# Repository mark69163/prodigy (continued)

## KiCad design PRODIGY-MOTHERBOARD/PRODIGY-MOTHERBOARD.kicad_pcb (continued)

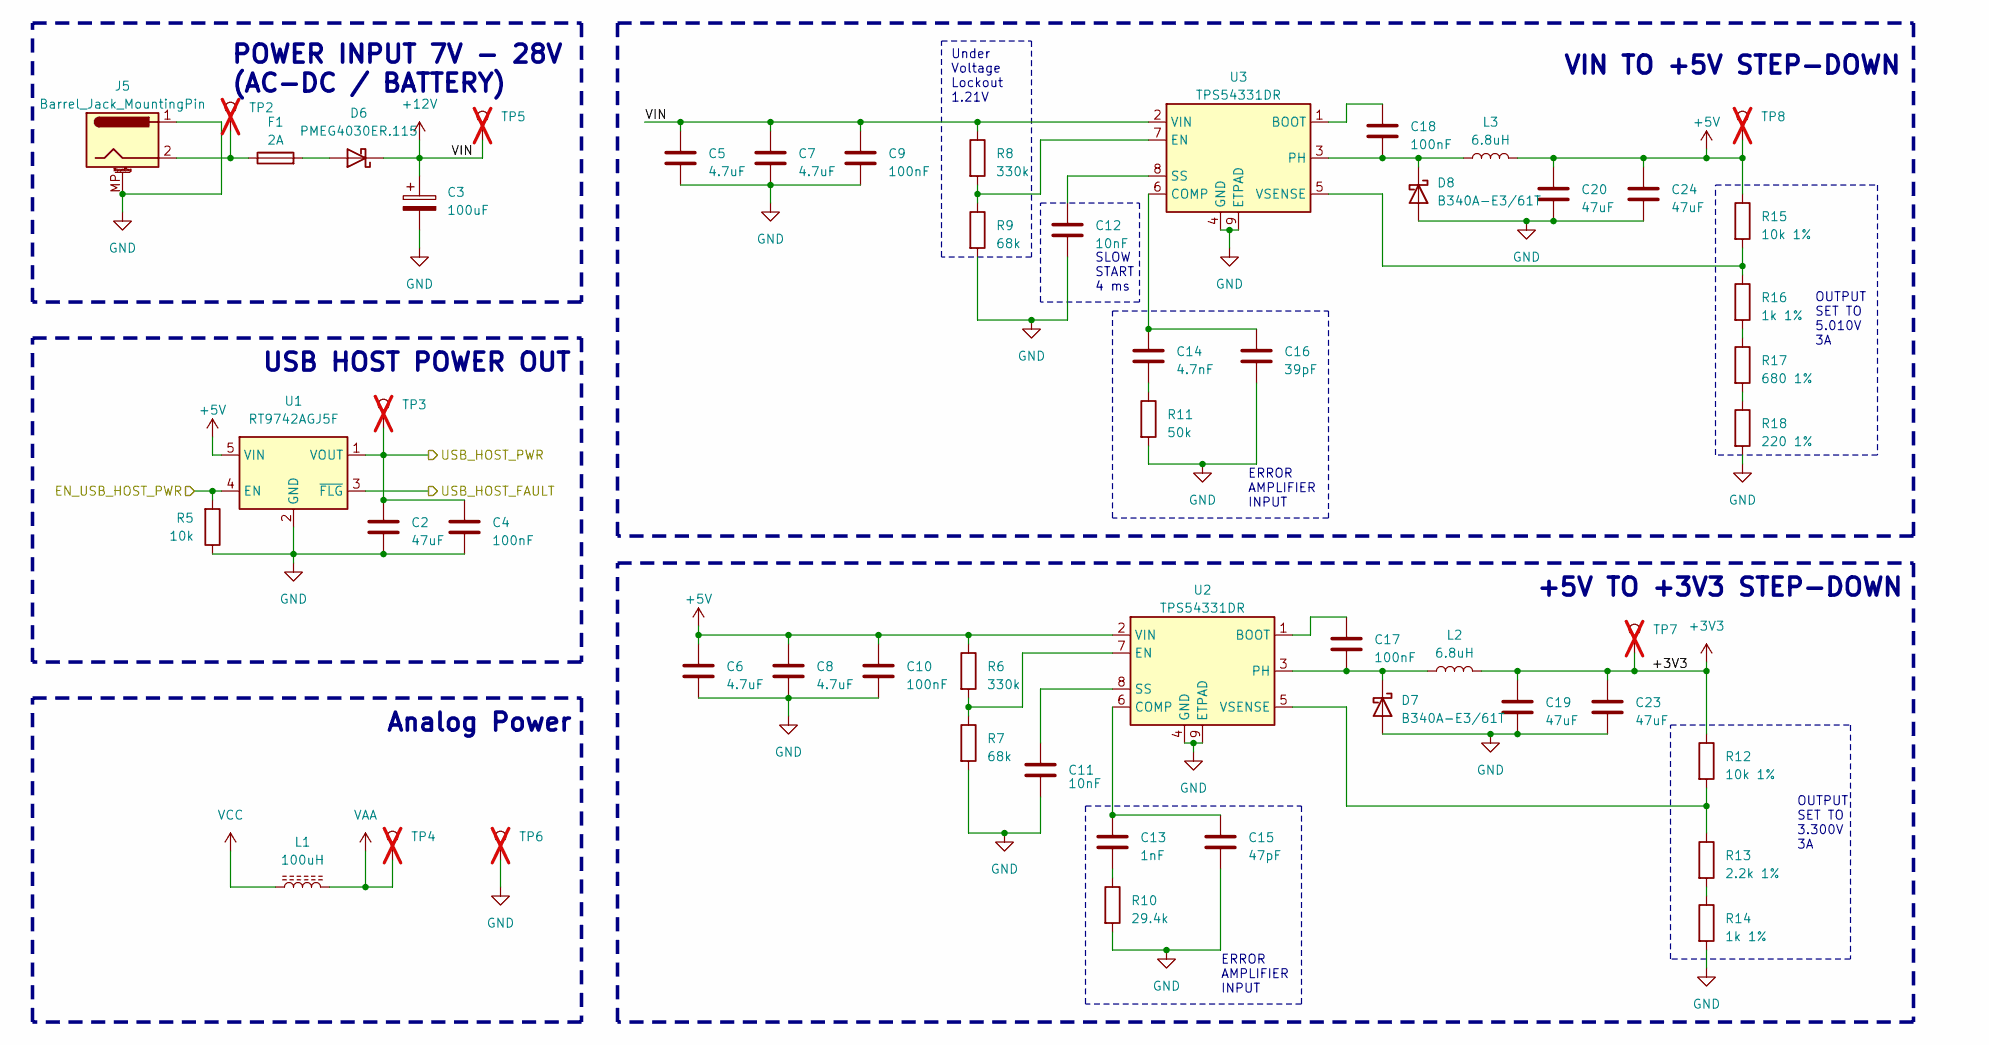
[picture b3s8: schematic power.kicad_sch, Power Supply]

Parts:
C2, C19, C20, C23, C24: 47uF; C_1210_3225Metric
C3: 100uF; CP_Elec_6.3x7.7
C4, C9, C10, C17, C18: 100nF; C_0603_1608Metric
C5, C6, C7, C8: 4.7uF; C_0805_2012Metric
C11, C12: 10nF; C_0603_1608Metric
C13: 1nF; C_0603_1608Metric
C14: 4.7nF; C_0603_1608Metric
C15: 47pF; C_0603_1608Metric
C16: 39pF; C_0603_1608Metric
D6: PMEG4030ER.115; Nexperia_CFP3_SOD-123W
D7, D8: B340A-E3/61T; D_SMA
F1: 2A; Fuse_1812_4532Metric
J5: Barrel_Jack_MountingPin; BarrelJack_Horizontal
L1: 100uH; L_1210_3225Metric
L2, L3: 6.8uH; L_Chilisin_BMRB00060624
R5: 10k; R_0603_1608Metric
R6, R8: 330k; R_0603_1608Metric
R7, R9: 68k; R_0603_1608Metric
R10: 29.4k; R_0603_1608Metric
R11: 50k; R_0603_1608Metric
R12, R15: 10k 1%; R_0603_1608Metric
R13: 2.2k 1%; R_0603_1608Metric
R14, R16: 1k 1%; R_0603_1608Metric
R17: 680 1%; R_0603_1608Metric
R18: 220 1%; R_0603_1608Metric
TP2, TP3, TP4, TP5, TP6, TP7, TP8: TestPoint_Pad_D3.0mm; not fitted
U1: RT9742AGJ5F; TSOT-23-5; MOUSER 835-RT9742AGJ5F
U2, U3: TPS54331DR; TI_SO-PowerPAD-8_ThermalVias

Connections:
+3V3: C19.1, C23.1, L2.2, R12.1, TP7.1; also elsewhere on the board
+5V: C6.1, C8.1, C10.1, C20.1, C24.1, L3.2, R6.1, R15.1, TP8.1, U1.5 (VIN), U2.2 (VIN); also elsewhere on the board
+12V: C3.1, C5.1, C7.1, C9.1, D6.1 (K), R8.1, TP5.1, U3.2 (VIN); also elsewhere on the board
/MCU/USB_HOST_ENABLE: R5.2, U1.4 (EN); also elsewhere on the board
/MCU/USB_HOST_FAULT: U1.3 (~FLG); also elsewhere on the board
/OUTPUTS/BREAKOUT_USB_VBUS: C2.1, C4.1, TP3.1, U1.1 (VOUT); also elsewhere on the board
GND: C2.2, C3.2, C4.2, C5.2, C6.2, C7.2, C8.2, C9.2, C10.2, C11.2, C12.2, C15.2, C16.2, C19.2, C20.2, C23.2, C24.2, D7.2 (A), D8.2 (A), J5.1, J5.MP (MountPin), R5.1, R7.2, R9.2, R10.2, R11.2, R14.2, R18.2, TP6.1, U1.2 (GND), U2.4 (GND), U2.9 (ETPAD), U3.4 (GND), U3.9 (ETPAD); also elsewhere on the board
unnamed: C13.2, R10.1
unnamed: C14.2, R11.1
unnamed: D6.2 (A), F1.2
unnamed: C17.2, D7.1 (K), L2.1, U2.3 (PH)
unnamed: C18.2, D8.1 (K), L3.1, U3.3 (PH)
unnamed: F1.1, J5.2, TP2.1
unnamed: R13.2, R14.1
unnamed: R16.2, R17.1
unnamed: R17.2, R18.1
unnamed: C17.1, U2.1 (BOOT)
unnamed: C13.1, C15.1, U2.6 (COMP)
unnamed: R6.2, R7.1, U2.7 (EN)
unnamed: C11.1, U2.8 (SS)
unnamed: R12.2, R13.1, U2.5 (VSENSE)
unnamed: C18.1, U3.1 (BOOT)
unnamed: C14.1, C16.1, U3.6 (COMP)
unnamed: R8.2, R9.1, U3.7 (EN)
unnamed: C12.1, U3.8 (SS)
unnamed: R15.2, R16.1, U3.5 (VSENSE)
VAA: L1.2, TP4.1; also elsewhere on the board
VCC: L1.1; also elsewhere on the board

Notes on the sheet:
+5V TO +3V3 STEP-DOWN
Analog Power
VIN TO +5V STEP-DOWN
SLOW START 4 ms
Under Voltage Lockout 1.21V
USB HOST POWER OUT
POWER INPUT 7V - 28V (AC-DC / BATTERY)
OUTPUT SET TO 5.010V 3A
ERROR AMPLIFIER INPUT
OUTPUT SET TO 3.300V 3A

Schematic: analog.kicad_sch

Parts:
C77: 22uF; C_0805_2012Metric
C78, C79: 470nF; C_0603_1608Metric
C80: 10pF; C_0603_1608Metric
C81: 47uF; C_1210_3225Metric
D65, D66, D67, D68, D69, D70, D71: SD05_SOD323; D_SOD-323
MK1: Mic; POM-2244P-C3310-2-R; MOUSER 497-MO093803-1
Q5: ALS-PDIC15-21B/TR8; Kingbright_KPS-3227
R62: 1k; R_0603_1608Metric
R63, R64, R67, R68: 10k; R_0603_1608Metric
R65: 47k; R_0603_1608Metric
R66: 1M; R_0805_2012Metric
RV2: 100k; Potentiometer_Alpha_RD901F-40-00D_Single_Vertical
RV3: 10k; 2-Axis-Joystick; MOUSER 485-2765
TH1: NTC 10k; R_0805_2012Metric
TP10, TP11, TP12, TP15: TestPoint_Pad_D3.0mm; not fitted
U20: NE5532; SOIC-8_3.9x4.9mm_P1.27mm

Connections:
/MCU/ANALOG_HEATER_TEMPERATURE: D71.2 (A2), R68.2, TH1.2, TP15.1; also elsewhere on the board
/MCU/ANALOG_JOYSTICK_X: D69.2 (A2), RV3.2 (RVX); also elsewhere on the board
/MCU/ANALOG_JOYSTICK_Y: D70.2 (A2), RV3.5 (RVY); also elsewhere on the board
/MCU/ANALOG_MICROPHONE: C80.2, R66.1, TP11.1, U20.1; also elsewhere on the board
/MCU/ANALOG_PHOTOTRANSISTOR: C81.1, D68.2 (A2), Q5.2, Q5.4, R67.2, TP12.1; also elsewhere on the board
/MCU/ANALOG_POTENTIOMETER: D67.2 (A2), RV2.2, TP10.1; also elsewhere on the board
GND: C77.2, C81.2, D65.1 (A1), D66.1 (A1), D67.1 (A1), D68.1 (A1), D69.1 (A1), D70.1 (A1), D71.1 (A1), MK1.1 (-), R64.1, R67.1, R68.1, RV2.1, RV3.3 (GND), RV3.6 (GND), U20.4 (V-), U20.5 (+), U20.6 (-); also elsewhere on the board
unnamed: C78.2, C79.2, R65.2
unnamed: C78.1, C79.1, D65.2 (A2), MK1.2 (+), R62.1
unnamed: R63.1, R64.2, U20.3 (+)
unnamed: C80.1, R65.1, R66.2, U20.2 (-)
VAA: C77.1, D66.2 (A2), Q5.1, Q5.3, R62.2, R63.2, RV2.3, RV3.1 (VIN), RV3.4 (VIN), TH1.1, U20.8 (V+); also elsewhere on the board

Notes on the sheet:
Potentiometer
Condensator Microphone with audio amplifier
NC-Thermistor
Phototransistor
2-Axis Joystick

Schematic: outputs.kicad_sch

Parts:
D14, D15, D16, D17, D18, D19, D20, D21, D22, D23, D24, D25, D26, D27, D28, D29, D30, D31, D32, D33, D34, D35, D36, D37, D38: SD05_SOD323; D_SOD-323
J9: A_IN; TerminalBlock_Phoenix_MKDS-1,5-2-5.08_1x02_P5.08mm_Horizont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
J10: RTD_PT100; TerminalBlock_Phoenix_MKDS-1,5-4-5.08_1x04_P5.08mm_Horizont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
J11: Can; TerminalBlock_Phoenix_MKDS-1,5-3-5.08_1x03_P5.08mm_Horizont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
J12: USB_A; USB_A_TE_292303-7_Horizontal; MOUSER 649-87583-0010RHLF
J13: SPI_OUT; TerminalBlock_Phoenix_MKDS-1,5-6-5.08_1x06_P5.08mm_Horizont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
J14: MOTOR; TerminalBlock_Phoenix_MKDS-1,5-6-5.08_1x06_P5.08mm_Horizont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
J15: 12V OUT; TerminalBlock_Phoenix_MKDS-1,5-2-5.08_1x02_P5.08mm_Horizont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
J16: Neopixel; TerminalBlock_Phoenix_MKDS-1,5-3-5.08_1x03_P5.08mm_Horizont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
J17: SERIAL; TerminalBlock_Phoenix_MKDS-1,5-4-5.08_1x04_P5.08mm_Horizont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
J18: I2C; TerminalBlock_Phoenix_MKDS-1,5-4-5.08_1x04_P5.08mm_Horizont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
R26: 220k; R_0603_1608Metric
U6: PCA9306DC; VSSOP-8_2.3x2mm_P0.5mm

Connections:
+5V: J13.5, J16.2, R26.1, U6.7 (VREF2); also elsewhere on the board
+12V: D33.2 (A2), J15.1; also elsewhere on the board
/50Hz Filter/IN_P1+: D18.2 (A2), J9.1; also elsewhere on the board
/50Hz Filter/IN_P1-: D21.2 (A2), J9.2; also elsewhere on the board
/CAN/CAN_H: D16.2 (A2), J11.1; also elsewhere on the board
/CAN/CAN_L: D19.2 (A2), J11.2; also elsewhere on the board
/I2C/I2C_SCL_5V: D37.2 (A2), J18.1; also elsewhere on the board
/I2C/I2C_SDA_5V: D38.2 (A2), J18.2; also elsewhere on the board
/MCU/MOTOR_CC_IN_1: D32.2 (A2), J14.1; also elsewhere on the board
/MCU/MOTOR_CC_IN_2: D30.2 (A2), J14.2; also elsewhere on the board
/MCU/SERIAL_OUT_RX2: U6.3 (SCL1); also elsewhere on the board
/MCU/SERIAL_OUT_TX2: U6.4 (SDA1); also elsewhere on the board
/MCU/USB_HOST_OUT_P+: D26.2 (A2), J12.3 (D+); also elsewhere on the board
/MCU/USB_HOST_OUT_P-: D29.2 (A2), J12.2 (D-); also elsewhere on the board
/MOTOR/MOTOR_OUT1_BREAKOUT_1: D27.2 (A2), J14.3; also elsewhere on the board
/MOTOR/MOTOR_OUT2_BREAKOUT_1: D24.2 (A2), J14.4; also elsewhere on the board
/OUTPUTS/BREAKOUT_NEOPIXEL_IN: D34.2 (A2), J16.1; also elsewhere on the board
/OUTPUTS/BREAKOUT_USB_VBUS: D23.2 (A2), J12.1 (VBUS); also elsewhere on the board
/OUTPUTS/RTD_W1: D14.2 (A2), J10.1; also elsewhere on the board
/OUTPUTS/RTD_W2: D15.2 (A2), J10.2; also elsewhere on the board
/OUTPUTS/RTD_W3: D17.2 (A2), J10.3; also elsewhere on the board
/OUTPUTS/RTD_W4: D20.2 (A2), J10.4; also elsewhere on the board
/SPI/CLK: D25.2 (A2), J13.2; also elsewhere on the board
/SPI/CS_BREAKOUT: D22.2 (A2), J13.1; also elsewhere on the board
/SPI/MISO: D31.2 (A2), J13.4; also elsewhere on the board
/SPI/MOSI: D28.2 (A2), J13.3; also elsewhere on the board
GND: D14.1 (A1), D15.1 (A1), D16.1 (A1), D17.1 (A1), D18.1 (A1), D19.1 (A1), D20.1 (A1), D21.1 (A1), D22.1 (A1), D23.1 (A1), D24.1 (A1), D25.1 (A1), D26.1 (A1), D27.1 (A1), D28.1 (A1), D29.1 (A1), D30.1 (A1), D31.1 (A1), D32.1 (A1), D33.1 (A1), D34.1 (A1), D35.1 (A1), D36.1 (A1), D37.1 (A1), D38.1 (A1), J11.3, J12.4 (GND), J12.5 (Shield), J13.6, J14.6, J15.2, J16.3, J17.4, J18.4, U6.1 (GND); also elsewhere on the board
unnamed: D35.2 (A2), J17.2, U6.5 (SDA2)
unnamed: D36.2 (A2), J17.1, U6.6 (SCL2)
unnamed: R26.2, U6.8 (EN)
VCC: J14.5, J17.3, J18.3, U6.2 (VREF1); also elsewhere on the board

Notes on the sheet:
I2C Breakout
12V Power Breakout
SPI Breakout
PT100/PT1000 Breakout
CAN Breakout
Piezo Sensor Input Breakout
Motor Breakout
Neopixel Breakout
USB HOST Breakout
SERIAL breakout with level shifter

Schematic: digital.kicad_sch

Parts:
BZ1: Buzzer; MagneticBuzzer_Kobitone_254-EMB84Q-RO; MOUSER 490-CMT-9504-87SMTTR
C64, C65, C66, C67, C68, C70, C71, C72: 100nF; C_0603_1608Metric
C69: DNP; R_0603_1608Metric; not fitted
C73, C74, C75, C76: 4.7uF; C_0805_2012Metric
D39, D40, D41, D54: LED_GREEN; LED_D3.0mm
D42, D44, D45, D46, D47, D51, D52, D53: WS2812B; LED_WS2812B_PLCC4_5.0x5.0mm_P3.2mm
D43: LL-304PDD2E; LED_D3.0mm_Horizontal_O1.27mm_Z2.0mm_IRBlack
D48, D49, D50: LED_RED; LED_D3.0mm
D55, D56, D61, D62: SD05_SOD323; D_SOD-323
D57, D58, D59, D63, D64: 1N4148W; D_SOD-323
D60: LED_BGAR; LED_D5.0mm-4_RGB
F2: 0.75A PTC; Fuse_1812_4532Metric
JP9: Debounce Selector; PinHeader_1x03_P2.54mm_Vertical
Q2, Q4: BC850; SOT-23
Q3: N-FET 1.4A; SOT-23
R38, R46, R48, R50, R51, R52, R53, R55, R56, R60, R61: 10k; R_0603_1608Metric
R39: 4.7k; R_0603_1608Metric
R40, R43, R44, R45, R54, R57, R58, R59: 1k; R_0603_1608Metric
R41, R47: 100; R_0603_1608Metric
R42: 39; R_0805_2012Metric
R49: 22; R_2512_6332Metric
SW3, SW4, SW5, SW6: SW_Push; SW_SPST_Omron_B3FS-105xP
U18: SN74LVC1T45DBV; SOT-23-6
U19: TSOP4836; Vishay_MOLD-3Pin

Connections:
+3V3: BZ1.1 (-), D41.2 (A), D59.1 (K), R42.2; also elsewhere on the board
+5V: C64.1, C65.1, C66.1, C67.1, C68.1, C70.1, C71.1, C72.1, D40.2 (A), D42.1 (VDD), D44.1 (VDD), D45.1 (VDD), D46.1 (VDD), D47.1 (VDD), D51.1 (VDD), D52.1 (VDD), D53.1 (VDD), U18.6 (VCCB); also elsewhere on the board
+12V: D39.2 (A), F2.1, R48.2; also elsewhere on the board
/MCU/DIGITAL_BUTTON_IN_0: JP9.2 (C); also elsewhere on the board
/MCU/DIGITAL_BUTTON_IN_1: C76.1, D64.1 (K), R61.2; also elsewhere on the board
/MCU/DIGITAL_BUTTON_IN_2: C73.1, D58.1 (K), R53.2; also elsewhere on the board
/MCU/DIGITAL_BUTTON_IN_3: C75.1, D63.1 (K), R60.2; also elsewhere on the board
/MCU/DIGITAL_BUZZER_OUT: R54.1; also elsewhere on the board
/MCU/DIGITAL_HEATER_OUT: R46.2, R47.1; also elsewhere on the board
/MCU/DIGITAL_IR_EMITTER: R41.1; also elsewhere on the board
/MCU/DIGITAL_IR_RECEIVER: C69.1, U19.1 (OUT); also elsewhere on the board
/MCU/DIGITAL_LED_OUT_0: D48.2 (A); also elsewhere on the board
/MCU/DIGITAL_LED_OUT_1: D49.2 (A); also elsewhere on the board
/MCU/DIGITAL_LED_OUT_2: D50.2 (A); also elsewhere on the board
/MCU/DIGITAL_NEOPIXEL_OUT: U18.3 (A); also elsewhere on the board
/MCU/DIGITAL_RGB_B: R59.1; also elsewhere on the board
/MCU/DIGITAL_RGB_G: R58.1; also elsewhere on the board
/MCU/DIGITAL_RGB_R: R57.1; also elsewhere on the board
/OUTPUTS/BREAKOUT_NEOPIXEL_IN: D51.2 (DOUT); also elsewhere on the board
GND: C64.2, C65.2, C66.2, C67.2, C68.2, C69.2, C70.2, C71.2, C72.2, C73.2, C74.2, C75.2, C76.2, D42.3 (VSS), D44.3 (VSS), D45.3 (VSS), D46.3 (VSS), D47.3 (VSS), D51.3 (VSS), D52.3 (VSS), D53.3 (VSS), D55.1 (A1), D56.1 (A1), D60.3 (A), D61.1 (A1), D62.1 (A1), Q2.2 (E), Q3.2 (S), Q4.2 (E), R38.1, R39.1, R40.1, R43.1, R44.1, R45.1, R46.1, SW3.1, SW4.1, SW5.1, SW6.1, U18.2 (GND), U18.5 (DIR), U19.2 (GND); also elsewhere on the board
unnamed: BZ1.2 (+), D59.2 (A), Q4.3 (C)
unnamed: D39.1 (K), R38.2
unnamed: D40.1 (K), R39.2
unnamed: D41.1 (K), R40.2
unnamed: D42.4 (DIN), D53.2 (DOUT)
unnamed: D42.2 (DOUT), D44.4 (DIN)
unnamed: D43.2 (A), R42.1
unnamed: D43.1 (K), Q2.3 (C)
unnamed: D44.2 (DOUT), D46.4 (DIN)
unnamed: D45.4 (DIN), U18.4 (B)
unnamed: D45.2 (DOUT), D47.4 (DIN)
unnamed: D46.2 (DOUT), D51.4 (DIN)
unnamed: D47.2 (DOUT), D52.4 (DIN)
unnamed: D48.1 (K), R43.2
unnamed: D49.1 (K), R44.2
unnamed: D50.1 (K), R45.2
unnamed: D52.2 (DOUT), D53.4 (DIN)
unnamed: D54.2 (A), R48.1
unnamed: D54.1 (K), Q3.3 (D), R49.2
unnamed: D55.2 (A2), D58.2 (A), R50.1, R53.1, SW3.2
unnamed: D56.2 (A2), D57.2 (A), JP9.3 (B), R51.1, R52.1, SW4.2
unnamed: C74.1, D57.1 (K), JP9.1 (A), R52.2
unnamed: D60.1 (BK), R59.2
unnamed: D60.2 (GK), R58.2
unnamed: D60.4 (RK), R57.2
unnamed: D61.2 (A2), D63.2 (A), R55.1, R60.1, SW5.2
unnamed: D62.2 (A2), D64.2 (A), R56.1, R61.1, SW6.2
unnamed: F2.2, R49.1
unnamed: Q2.1 (B), R41.2
unnamed: Q3.1 (G), R47.2
unnamed: Q4.1 (B), R54.2
VCC: R50.2, R51.2, R55.2, R56.2, U18.1 (VCCA), U19.3 (Vs); also elsewhere on the board

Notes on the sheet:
~500mA
Infrared Emitter
NEOPIXEL chain
Buzzer
USER RGB
Indicator LEDs
Infrared Receiver
USER Buttons
USER LEDs
Heater

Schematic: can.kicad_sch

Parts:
C26: 100nF; C_0603_1608Metric
C27, C28, C29, C30: 100pF; C_0603_1608Metric
C31: 4.7nF; C_0603_1608Metric
L4: ACM7060-701-2PL-TL; L_CommonModeChoke_TDK_ACM7060
R23, R24: 59; R_0603_1608Metric
TP9: TestPoint_Pad_D3.0mm; not fitted
U4: TJA1051T-E; SOIC-8_3.9x4.9mm_P1.27mm

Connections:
+3.3V: C26.1, U4.3 (VCC); also elsewhere on the board
/CAN/CAN_EN: TP9.1, U4.5 (EN); also elsewhere on the board
/CAN/CAN_H: C29.1, L4.1, R23.1; also elsewhere on the board
/CAN/CAN_L: C30.1, L4.2, R24.2; also elsewhere on the board
/CAN/CAN_RX: U4.4 (RXD); also elsewhere on the board
/CAN/CAN_SILENT: U4.8 (S); also elsewhere on the board
/CAN/CAN_TX: U4.1 (TXD); also elsewhere on the board
GND: C26.2, C27.2, C28.2, C29.2, C30.2, C31.2, U4.2 (GND); also elsewhere on the board
unnamed: C31.1, R23.2, R24.1
unnamed: C27.1, L4.4, U4.7 (CANH)
unnamed: C28.1, L4.3, U4.6 (CANL)

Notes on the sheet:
Isolation
120 Ohm Termination

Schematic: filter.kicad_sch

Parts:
C82, C86: 10uF; C_0805_2012Metric
C83: 100nF; C_0603_1608Metric
C84: 100nF C0G; C_1206_3216Metric
C85: 47uF; C_1210_3225Metric
R69, R70, R76: 1k; R_0603_1608Metric
R71: 68k; R_0603_1608Metric
R72: 100; R_0603_1608Metric
R73, R74, R75: 220k; R_0603_1608Metric
RV4: 2k; Potentiometer_Bourns_3314J_Vertical
TP16: A1; TestPoint_Pad_D3.0mm; not fitted
U21: MCP6021RT-E/OT; SOT-23-5

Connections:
/50Hz Filter/ANALOG_BREAKOUT_OUT: R75.1, TP16.1, U21.1; also elsewhere on the board
/50Hz Filter/IN_P1+: R69.1; also elsewhere on the board
/50Hz Filter/IN_P1-: R70.1; also elsewhere on the board
GND: C82.2, C83.2, C84.2, R70.2, R71.2, R74.2, R76.2, U21.2 (V-); also elsewhere on the board
unnamed: C84.1, C85.1, R72.2
unnamed: C86.2, RV4.1
unnamed: R69.2, R71.1, R72.1
unnamed: R76.1, RV4.2
unnamed: C85.2, R73.2, R74.1, U21.3 (+)
unnamed: C86.1, R75.2, U21.4 (-)
VAA: C82.1, C83.1, R73.1, U21.5 (V+); also elsewhere on the board

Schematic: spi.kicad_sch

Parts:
RN3, RN4, RN5: R_Pack04; R_Array_Convex_4x0603
U13: TXS0108EPW; TSSOP-20_4.4x6.5mm_P0.65mm

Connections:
+5V: RN5.5 (R4.2), RN5.6 (R3.2), RN5.7 (R2.2), RN5.8 (R1.2), U13.19 (VCCB); also elsewhere on the board
/MCU/SPI_CS_BREAKOUT: RN3.1 (R1.1), U13.9 (A8); also elsewhere on the board
/MCU/SPI_CS_NFC: RN4.3 (R3.1); also elsewhere on the board
/MCU/SPI_CS_SEVENSEG: RN3.2 (R2.1), U13.8 (A7); also elsewhere on the board
/MCU/SPI_CS_TFT: RN4.1 (R1.1); also elsewhere on the board
/MCU/SPI_MISO: RN3.3 (R3.1), U13.6 (A5); also elsewhere on the board
/MCU/SPI_MOSI: RN3.4 (R4.1), U13.5 (A4); also elsewhere on the board
/MCU/SPI_RST_NFC: RN4.4 (R4.1); also elsewhere on the board
/MCU/SPI_SCK: U13.7 (A6); also elsewhere on the board
/MCU/SPI_TFT_RESET: RN4.2 (R2.1); also elsewhere on the board
/SPI/CLK: U13.14 (B6); also elsewhere on the board
/SPI/CS_BREAKOUT: RN5.4 (R4.1), U13.12 (B8); also elsewhere on the board
/SPI/CS_SEVENSEG: RN5.3 (R3.1), U13.13 (B7); also elsewhere on the board
/SPI/MISO: RN5.2 (R2.1), U13.15 (B5); also elsewhere on the board
/SPI/MOSI: RN5.1 (R1.1), U13.16 (B4); also elsewhere on the board
GND: U13.11 (GND); also elsewhere on the board
VCC: RN3.5 (R4.2), RN3.6 (R3.2), RN3.7 (R2.2), RN3.8 (R1.2), RN4.5 (R4.2), RN4.6 (R3.2), RN4.7 (R2.2), RN4.8 (R1.2), U13.2 (VCCA), U13.10 (OE); also elsewhere on the board

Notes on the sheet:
SPI OUT PULLUP
SPI IN PULLUP

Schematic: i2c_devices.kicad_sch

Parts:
C34, C35, C38, C39: 100nF; C_0603_1608Metric
C36, C37, C40: 10uF; C_0805_2012Metric
DS1: WC1602A
FID14: Fiducial; Fiducial_1mm_Mask3mm; not fitted
J19: KEYPAD_MATRIX; PinHeader_1x08_P2.54mm_Vertical_SMD_Pin1Left
J20: OLED; PinSocket_1x04_P2.54mm_Vertical
JP3, JP4: A2_Jumper; SolderJumper-2_P1.3mm_Open_Pad1.0x1.5mm; not fitted
JP5, JP6: A1_Jumper; SolderJumper-2_P1.3mm_Open_Pad1.0x1.5mm; not fitted
JP7, JP8: A0_Jumper; SolderJumper-2_P1.3mm_Open_Pad1.0x1.5mm; not fitted
Q1: BC850; SOT-23
RN1, RN2: R_Pack04; R_Array_Convex_4x0603
RV1: 10k; Potentiometer_Bourns_3314J_Vertical
U9, U10: PCF8574; SSOP-20_4.4x6.5mm_P0.65mm
U11: HDC1080; Texas_PWSON-N6; MOUSER 595-HDC1080DMBR
U12: LIS2DH12TR; LGA-12_2x2mm_P0.5mm; MOUSER 511-LIS2DH12TR

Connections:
+3V3: C37.1, C38.1, C39.1, U11.5 (VCC), U12.9 (Vdd), U12.10 (Vdd_IO); also elsewhere on the board
+5V: C34.1, C35.1, C36.1, C40.1, DS1.2 (VDD), DS1.15 (LED(+)), J20.3, RN1.5 (R4.2), RN1.6 (R3.2), RN1.7 (R2.2), RN1.8 (R1.2), RN2.5 (R4.2), RN2.6 (R3.2), RN2.7 (R2.2), RN2.8 (R1.2), RV1.3, U9.16 (VDD), U10.16 (VDD); also elsewhere on the board
/I2C/I2C Devices/INTERRUPT_KEYPAD: RN2.1 (R1.1), U10.13 (~INT); also elsewhere on the board
/I2C/I2C_SCL_3V3: U11.6 (SCL), U12.1 (SCL/SPC); also elsewhere on the board
/I2C/I2C_SCL_5V: J20.2, U9.14 (SCL), U10.14 (SCL); also elsewhere on the board
/I2C/I2C_SDA_3V3: U11.1 (SDA), U12.4 (SDA/SDI); also elsewhere on the board
/I2C/I2C_SDA_5V: J20.1, U9.15 (SDA), U10.15 (SDA); also elsewhere on the board
/I2C/INTERRRUPT_ACCELEROMETER: U12.12 (INT1); also elsewhere on the board
GND: C34.2, C35.2, C36.2, C37.2, C38.2, C39.2, C40.2, DS1.1 (VSS), J20.4, JP3.1 (A), JP4.1 (A), JP5.1 (A), JP6.1 (A), JP7.1 (A), JP8.1 (A), Q1.2 (E), RV1.1, U9.8 (VSS), U10.8 (VSS), U11.2 (GND), U12.5 (RES), U12.6 (GND), U12.7 (GND), U12.8 (GND); also elsewhere on the board
unnamed: DS1.11 (D4), U9.9 (P4)
unnamed: DS1.12 (D5), U9.10 (P5)
unnamed: DS1.13 (D6), U9.11 (P6)
unnamed: DS1.14 (D7), U9.12 (P7)
unnamed: DS1.6 (E), U9.6 (P2)
unnamed: DS1.16 (LED(-)), Q1.3 (C)
unnamed: DS1.4 (RS), U9.4 (P0)
unnamed: DS1.5 (R/W), U9.5 (P1)
unnamed: DS1.3 (VO), RV1.2
unnamed: J19.1, U10.4 (P0)
unnamed: J19.2, U10.5 (P1)
unnamed: J19.3, U10.6 (P2)
unnamed: J19.4, U10.7 (P3)
unnamed: J19.5, U10.9 (P4)
unnamed: J19.6, U10.10 (P5)
unnamed: J19.7, U10.11 (P6)
unnamed: J19.8, U10.12 (P7)
unnamed: JP3.2 (B), RN1.2 (R2.1), U9.3 (A2)
unnamed: JP4.2 (B), RN2.2 (R2.1), U10.3 (A2)
unnamed: JP5.2 (B), RN1.3 (R3.1), U9.2 (A1)
unnamed: JP6.2 (B), RN2.3 (R3.1), U10.2 (A1)
unnamed: JP7.2 (B), RN1.4 (R4.1), U9.1 (A0)
unnamed: JP8.2 (B), RN2.4 (R4.1), U10.1 (A0)
unnamed: Q1.1 (B), RN1.1 (R1.1), U9.7 (P3)

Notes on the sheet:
LCD with I2C I/O Expander
Keypad Matrix with I2C I/O Expander
Accelerometer and Gyroscope
Temperature and Humidity Sensor
Oled Breakout 128x32

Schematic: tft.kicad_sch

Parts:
U17: CR2013-MI2120

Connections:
/MCU/SPI_CS_TFT: U17.3 (~CS); also elsewhere on the board
/MCU/SPI_MISO: U17.9 (MISO); also elsewhere on the board
/MCU/SPI_MOSI: U17.6 (MOSI); also elsewhere on the board
/MCU/SPI_SCK: U17.7 (SCK); also elsewhere on the board
/MCU/SPI_TFT_DC: U17.5 (D/~C); also elsewhere on the board
/MCU/SPI_TFT_RESET: U17.4 (RESET); also elsewhere on the board
GND: U17.2 (GND); also elsewhere on the board
VCC: U17.1 (VCC), U17.8 (LED); also elsewhere on the board

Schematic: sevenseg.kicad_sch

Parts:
C41: 10uF; C_0805_2012Metric
C42: 100nF; C_0603_1608Metric
R32: 33k; R_0603_1608Metric
U14: MAX7219 / tm1637; SOIC-24W_7.5x15.4mm_P1.27mm
U15: CC56-12YWA; 4_digit_7_segment_display

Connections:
+5V: C41.1, C42.1, R32.1, U14.19 (V+); also elsewhere on the board
/SPI/CLK: U14.13 (CLK); also elsewhere on the board
/SPI/CS_SEVENSEG: U14.12 (LOAD); also elsewhere on the board
/SPI/MOSI: U14.1 (DIN); also elsewhere on the board
GND: C41.2, C42.2, U14.4 (GND), U14.9 (GND); also elsewhere on the board
unnamed: U14.2 (DIG_0), U15.12 (CC1)
unnamed: U14.11 (DIG_1), U15.9 (CC2)
unnamed: U14.6 (DIG_2), U15.8 (CC3)
unnamed: U14.7 (DIG_3), U15.6 (CC4)
unnamed: R32.2, U14.18 (ISET)
unnamed: U14.14 (SEG_A), U15.11 (a)
unnamed: U14.16 (SEG_B), U15.7 (b)
unnamed: U14.20 (SEG_C), U15.4 (c)
unnamed: U14.23 (SEG_D), U15.2 (d)
unnamed: U14.22 (SEG_DP), U15.3 (DPX)
unnamed: U14.21 (SEG_E), U15.1 (e)
unnamed: U14.15 (SEG_F), U15.10 (f)
unnamed: U14.17 (SEG_G), U15.5 (g)

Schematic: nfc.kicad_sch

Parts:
AE1: 13.56MHz 2.3Ohm 2.02uH; 40x40 antenna; not fitted
C43, C46, C47, C48, C49, C52: 100nF; C_0603_1608Metric
C44, C45: 4.7uF; C_0805_2012Metric
C50, C51, C57, C58: 22pF; C_0603_1608Metric
C53: 1nF; C_0603_1608Metric
C54, C55: 220pF; C_0603_1608Metric
C56, C59, C62, C63: 4.7pF; C_0603_1608Metric
C60, C61: 100pF; C_0603_1608Metric
L5, L6: 560nH; L_0603_1608Metric
R33: 10k; R_0603_1608Metric
R34: 1k; R_0603_1608Metric
R35: 2.7k; R_0603_1608Metric
R36, R37: 3R3; R_0603_1608Metric
U16: PN5321A3HN_C1xx; HVQFN-40-1EP_6x6mm_P0.5mm_EP4.1x4.1mm; MOUSER 771-PN5321A3HNC10
Y1: 27.12MHz; Crystal_SMD_SeikoEpson_FA128-4Pin_2.0x1.6mm

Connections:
+3V3: C43.1, C44.1, C45.1, C46.1, C47.1, C48.1, C49.1, R33.1, U16.5 (TVDD), U16.8 (AVDD), U16.16 (I0), U16.23 (PVDD), U16.39 (DVDD), U16.40 (VBAT); also elsewhere on the board
/MCU/SPI_CS_NFC: U16.27 (NSS/P50_SCL/HSU_RX); also elsewhere on the board
/MCU/SPI_IRQ_NFC: U16.25 (P70_IRQ); also elsewhere on the board
/MCU/SPI_MISO: U16.29 (MISO/P71); also elsewhere on the board
/MCU/SPI_MOSI: U16.28 (MOSI/SDA/HSU_TX); also elsewhere on the board
/MCU/SPI_RST_NFC: U16.26 (~RSTOUT); also elsewhere on the board
/MCU/SPI_SCK: U16.30 (SCK/P72); also elsewhere on the board
GND: C43.2, C44.2, C45.2, C46.2, C47.2, C48.2, C49.2, C50.2, C51.2, C52.2, C54.2, C55.1, C60.2, C61.1, C62.2, C63.1, U16.1 (DVSS), U16.3 (TVSS1), U16.7 (TVSS2), U16.11 (AVSS), U16.17 (I1), U16.18 (TESTEN), U16.41 (AVSS), Y1.2, Y1.4; also elsewhere on the board
unnamed: AE1.1, AE1.2, R36.1, R37.1
unnamed: C53.2, R35.1
unnamed: C54.1, C56.1, C57.1, L5.2, R35.2
unnamed: C55.2, C58.1, C59.1, L6.2
unnamed: C56.2, C57.2, C60.1, C62.1, R36.2
unnamed: C58.2, C59.2, C61.2, C63.2, R37.2
unnamed: C50.1, U16.14 (OSCIN), Y1.1
unnamed: C51.1, U16.15 (OSCOUT), Y1.3
unnamed: C53.1, R34.1, U16.10 (RX)
unnamed: L5.1, U16.4 (TX1)
unnamed: L6.1, U16.6 (TX2)
unnamed: C52.1, R34.2, U16.9 (VMID)
unnamed: R33.2, U16.38 (~RSTPD)

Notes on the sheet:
EMC Filter
HOST Interface Set to SPI
Bypass Caps
Voltage Ref
Antenna Matching

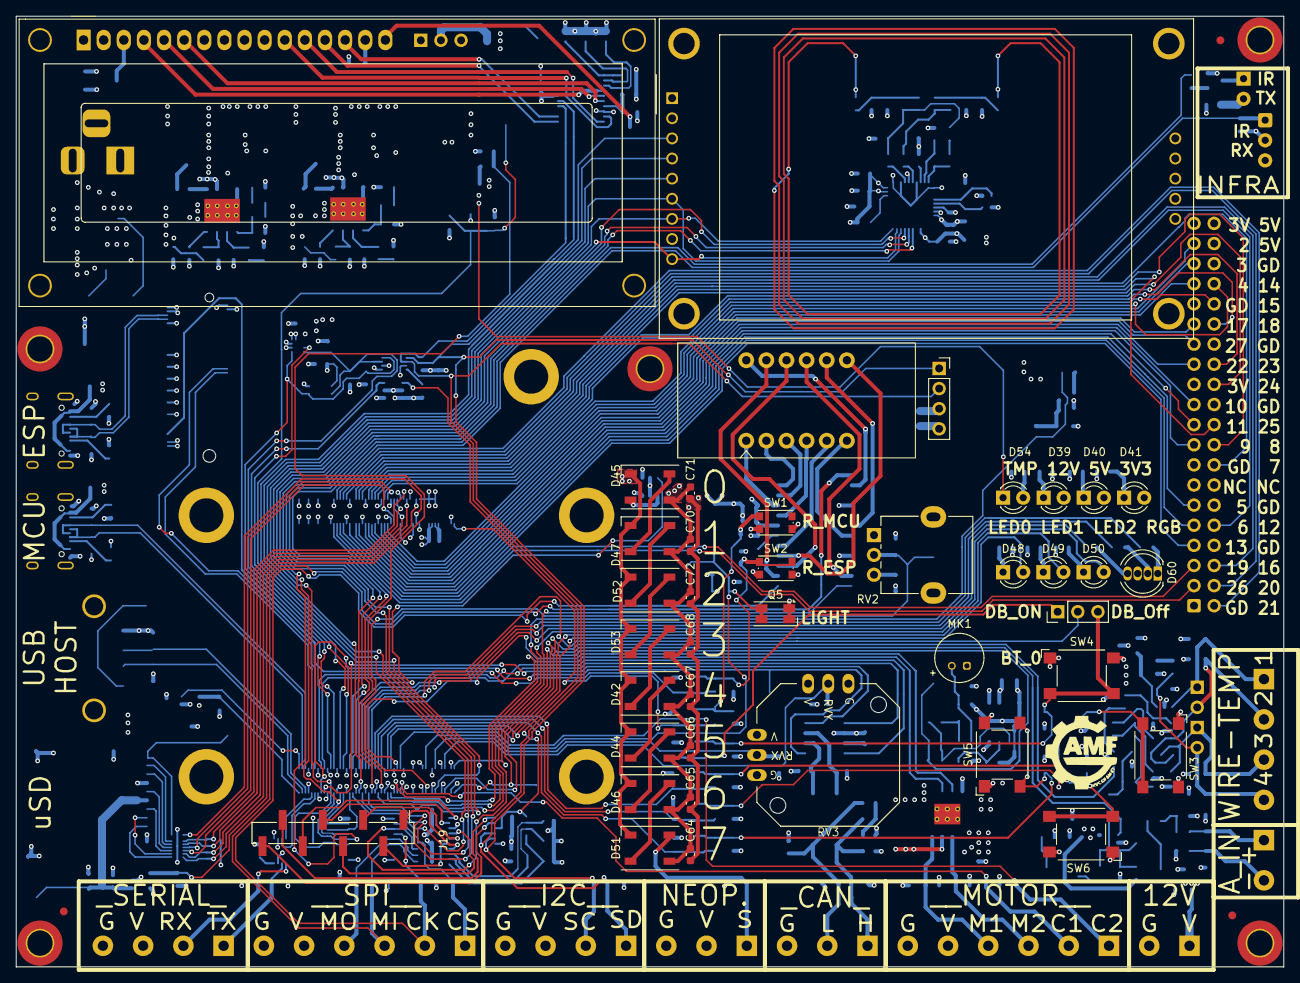
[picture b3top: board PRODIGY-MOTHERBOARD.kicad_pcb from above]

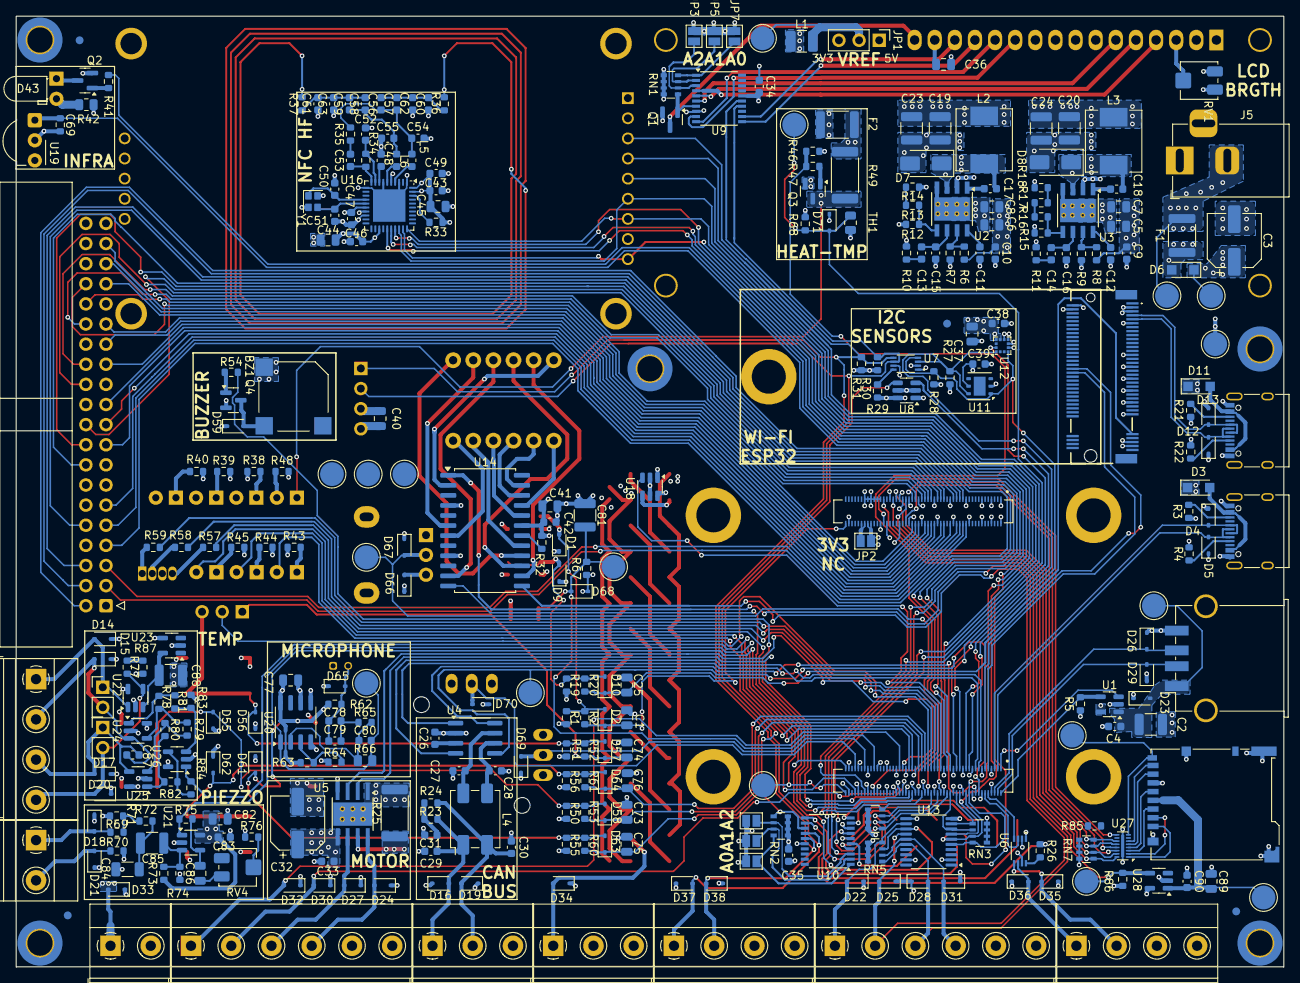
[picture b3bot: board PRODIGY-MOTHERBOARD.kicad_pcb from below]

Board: 4 copper layers, 160.0 x 120.0 mm, 373 parts (320 on the bottom side), 259 nets.

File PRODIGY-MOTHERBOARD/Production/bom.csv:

Designator,Footprint,Quantity,Value,LCSC Part #
BZ1,MagneticBuzzer_Kobitone_254-EMB84Q-RO,1,Buzzer,
"C1, C25, C44, C45, C5, C6, C7, C73, C74, C75, C76, C8",0805,12,4.7uF,
"C10, C17, C18, C26, C33, C34, C35, C38, C39, C4, C42, C43, C46, C47, C48, C49, C52, C64, C65, C66, C67, C68, C70, C71, C72, C83, C87, C9, C90",0603,29,100nF,
"C11, C12",0603,2,10nF,
"C13, C53",0603,2,1nF,
"C14, C31",0603,2,4.7nF,
C15,0603,1,47pF,
C16,0603,1,39pF,
"C19, C2, C20, C23, C24, C81, C85, C88",1210,8,47uF,
"C27, C28, C29, C30, C60, C61",0603,6,100pF,
"C3, C32",CP_Elec_6.3x7.7,2,100uF,
"C36, C37, C40, C41, C82, C86, C89",0805,7,10uF,
"C50, C51, C57, C58",0603,4,22pF,
"C54, C55",0603,2,220pF,
"C56, C59, C62, C63",0603,4,4.7pF,
C77,0805,1,22uF,
"C78, C79",0603,2,470nF,
C80,0603,1,10pF,
C84,1206,1,100nF C0G,
"D1, D12, D13, D14, D15, D16, D17, D18, D19, D20, D21, D22, D23, D24, D25, D26, D27, D28, D29, D30, D31, D32, D33, D34, D35, D36, D37, D38, D4, D5, D55, D56, D61, D62, D65, D66, D67, D68, D69, D70, D71, D9",D_SOD-323,42,SD05_SOD323,
"D10, D2, D57, D58, D59, D63, D64",D_SOD-323,7,1N4148W,
"D11, D3, D6",Nexperia_CFP3_SOD-123W,3,PMEG4030ER.115,
"D39, D40, D41, D54",LED_D3.0mm,4,LED_GREEN,
"D42, D44, D45, D46, D47, D51, D52, D53",LED_WS2812B_PLCC4_5.0x5.0mm_P3.2mm,8,WS2812B,
D43,LED_D3.0mm_Horizontal_O1.27mm_Z2.0mm_IRBlack,1,LL-304PDD2E,
"D48, D49, D50",LED_D3.0mm,3,LED_RED,
D60,LED_D5.0mm-4_RGB,1,LED_BGAR,
"D7, D8",D_SMA,2,B340A-E3/61T,
DS1,WC1602A,1,WC1602A,
F1,2920,1,2A,
F2,1812,1,0.75A PTC,
"H10, H6, H7, H8, H9",MountingHole_4.3mm_M4_ISO14580_Pad,5,MountingHole,
"J1, J4",HIROSE_DF40C-100DS-0.4V_51_,2,DF40C-100DS-0.4V(51),
J10,"TerminalBlock_Phoenix_MKDS-1,5-4-5.08_1x04_P5.08mm_Horizontal",1,RTD_PT100,
J11,"TerminalBlock_Phoenix_MKDS-1,5-3-5.08_1x03_P5.08mm_Horizontal",1,Can,
J12,USB_A_TE_292303-7_Horizontal,1,USB_A,
J13,"TerminalBlock_Phoenix_MKDS-1,5-6-5.08_1x06_P5.08mm_Horizontal",1,SPI_OUT,
J14,"TerminalBlock_Phoenix_MKDS-1,5-6-5.08_1x06_P5.08mm_Horizontal",1,MOTOR,
J15,"TerminalBlock_Phoenix_MKDS-1,5-2-5.08_1x02_P5.08mm_Horizontal",1,12V OUT ,
J16,"TerminalBlock_Phoenix_MKDS-1,5-3-5.08_1x03_P5.08mm_Horizontal",1,Neopixel,
J17,"TerminalBlock_Phoenix_MKDS-1,5-4-5.08_1x04_P5.08mm_Horizontal",1,SERIAL,
J18,"TerminalBlock_Phoenix_MKDS-1,5-4-5.08_1x04_P5.08mm_Horizontal",1,I2C,
J19,PinHeader_1x08_P2.54mm_Vertical_SMD_Pin1Left,1,KEYPAD_MATRIX,
"J2, J6",USB_C_Receptacle_XKB_U262-16XN-4BVC11,2,USB_C_Receptacle,
J20,PinSocket_1x04_P2.54mm_Vertical,1,OLED,
J21,microSD_HC_Hirose_DM3BT-DSF-PEJS,1,DM3BT-DSF-PEJS/C,
J3,IDC-Header_2x20_P2.54mm_Horizontal,1,Conn_02x20_Odd_Even,
J5,BarrelJack_Horizontal,1,Barrel_Jack_MountingPin,
J7,121992304,1,Bus_M.2_Socket_B,
J9,"TerminalBlock_Phoenix_MKDS-1,5-2-5.08_1x02_P5.08mm_Horizontal",1,A_IN,
JP1,PinHeader_1x03_P2.54mm_Vertical,1,VREF_Selector,
"JP10, JP11",PinHeader_1x02_P2.54mm_Vertical,2,Jumper_2_Open,
JP9,PinHeader_1x03_P2.54mm_Vertical,1,Debounce Selector,
L1,1210,1,100uH,
"L2, L3",L_Chilisin_BMRB00060624,2,6.8uH,
L4,L_CommonModeChoke_TDK_ACM7060,1,ACM7060-701-2PL-TL,
"L5, L6",0603,2,560nH,
MK1,POM-2244P-C3310-2-R,1,Mic,
"Q1, Q2, Q4",SOT-23,3,BC850,
Q3,SOT-23,1,N-FET 1.4A,
Q5,Kingbright_KPS-3227,1,ALS-PDIC15-21B/TR8,
"R1, R19, R2, R20, R33, R38, R46, R48, R5, R50, R51, R52, R53, R55, R56, R60, R61, R63, R64, R67, R68, R78, R80, R81, R82, R83, R84, R86",0603,28,10k,
R10,0603,1,29.4k,
R11,0603,1,50k,
"R12, R15",0603,2,10k 1%,
R13,0603,1,2.2k 1%,
"R14, R16",0603,2,1k 1%,
R17,0603,1,680 1%,
R18,0603,1,220 1%,
"R21, R22, R3, R4",0603,4,5.1k,
"R23, R24",0603,2,59,
R25,2512,1,2,
"R26, R29, R73, R74, R75",0603,5,220k,
"R27, R28, R30, R31, R39",0603,5,4.7k,
R32,0603,1,33k,
"R34, R40, R43, R44, R45, R54, R57, R58, R59, R62, R69, R70, R76, R87",0603,14,1k,
R35,0603,1,2.7k,
"R36, R37",0603,2,3R3,
"R41, R47, R72",0603,3,100,
R42,0805,1,39,
R49,2512,1,22,
"R6, R8",0603,2,330k,
R65,0603,1,47k,
R66,0805,1,1M,
"R7, R71, R9",0603,3,68k,
R77,0603,1,1k5,
R79,0603,1,3.205k,
"RN1, RN2, RN3, RN4, RN5, RN7",R_Array_Convex_4x0603,6,R_Pack04,
RV1,Potentiometer_Bourns_3314J_Vertical,1,10k,
RV2,Potentiometer_Alpha_RD901F-40-00D_Single_Vertical,1,100k,
RV3,2-Axis-Joystick,1,10k,
RV4,Potentiometer_Bourns_3314J_Vertical,1,2k,
"SW1, SW2",SW_Push_1P1T_NO_CK_KMR2,2,SW_Push,
"SW3, SW4, SW5, SW6",SW_SPST_Omron_B3FS-105xP,4,SW_Push,
TH1,0805,1,NTC 10k,
"U1, U28",TSOT-23-5,2,RT9742AGJ5F,
"U10, U9",SSOP-20_4.4x6.5mm_P0.65mm,2,PCF8574,
U11,Texas_PWSON-N6,1,HDC1080,
U12,LGA-12_2x2mm_P0.5mm,1,LIS2DH12TR,
U13,TSSOP-20_4.4x6.5mm_P0.65mm,1,TXS0108EPW,
U14,SOIC-24W_7.5x15.4mm_P1.27mm,1,MAX7219 / tm1637,
U15,4_digit_7_segment_display,1,CC56-12YWA,
U16,HVQFN-40-1EP_6x6mm_P0.5mm_EP4.1x4.1mm,1,PN5321A3HN_C1xx,
U17,CR2013-MI2120,1,CR2013-MI2120,
"U18, U8",SOT-23-6,2,SN74LVC1T45DBV,
U19,Vishay_MOLD-3Pin,1,TSOP4836,
"U2, U3",TI_SO-PowerPAD-8_ThermalVias,2,TPS54331DR,
U20,SOIC-8_3.9x4.9mm_P1.27mm,1,NE5532,
U21,SOT-23-5,1,MCP6021RT-E/OT,
"U22, U24, U25, U26",TSOT-23-5,4,LMP2011,
U23,SOT-23-5,1,LM4125AIM5-2.5,
U27,Nexperia_HUSON-16_USON-16-1EP_1.35x3.3mm_P0.4mm_EP0.4x2.8mm,1,IP4252CZ16,
U4,SOIC-8_3.9x4.9mm_P1.27mm,1,TJA1051T-E,
U5,Texas_HTSOP-8-1EP_3.9x4.9mm_P1.27mm_EP2.95x4.9mm_Mask2.4x3.1mm_ThermalVias,1,DRV8870DDA,
"U6, U7",VSSOP-8_2.3x2mm_P0.5mm,2,PCA9306DC,
Y1,Crystal_SMD_SeikoEpson_FA128-4Pin_2.0x1.6mm,1,27.12MHz,

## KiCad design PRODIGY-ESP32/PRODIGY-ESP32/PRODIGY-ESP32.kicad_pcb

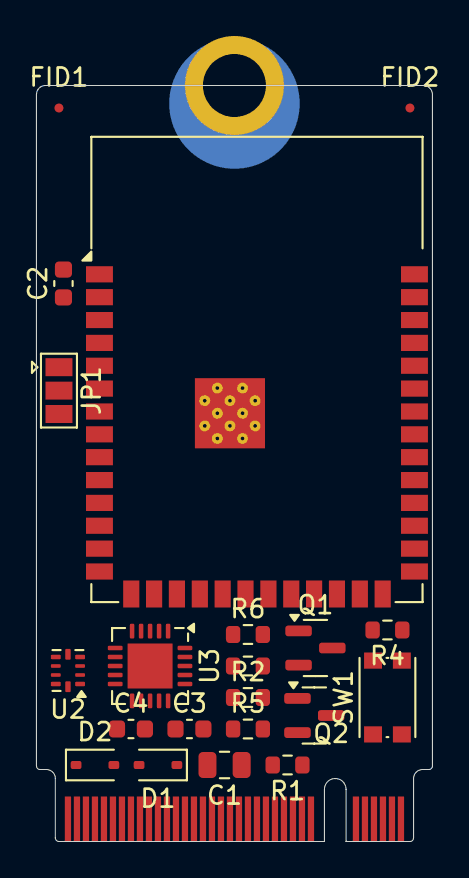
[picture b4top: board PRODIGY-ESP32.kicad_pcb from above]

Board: 2 copper layers, 22.0 x 42.0 mm, 22 parts (0 on the bottom side), 20 nets, no tracks yet.

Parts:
C1: 10uF; C_0805_2012Metric
C2, C3, C4: 100nF; C_0603_1608Metric
D1, D2: SD05_SOD323; D_SOD-323
FID1, FID2: Fiducial; Fiducial_0.5mm_Mask1.5mm
J1: Bus_M.2_Socket_B; M.2-B-KEY
JP1: Jumper_3_Bridged12; SolderJumper-3_P1.3mm_Open_Pad1.0x1.5mm
Q1, Q2: BC850; SOT-23
R1, R2, R3: 10k; R_0603_1608Metric
R4: 1k; R_0603_1608Metric
R5, R6: 0R; R_0603_1608Metric
SW1: SW_Push; SW_Push_1P1T_NO_CK_KMR2
U1: ESP32-S3-WROOM-1
U2: TS3USB221AQRSERQ1; Texas_UQFN-10_1.5x2mm_P0.5mm
U3: FT231XQ; QFN-20-1EP_4x4mm_P0.5mm_EP2.5x2.5mm

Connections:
+3V3: C1.1, C2.1, C3.1, C4.1, JP1.1 (A), R1.2, U1.2 (3V3), U2.10 (VCC), U3.10 (3V3OUT), U3.12 (VCC), U3.20 (VCCIO)
/DTR: Q2.2 (E), R2.1, U3.18 (~DTR)
/ESP_BUTTON_BOOT: Q2.3 (C), R4.2, U1.27 (IO0)
/ESP_BUTTON_RESET: Q1.3 (C), U1.3 (EN)
/ESP_SERIAL_RX0: R6.2, U1.36 (RXD0)
/ESP_SERIAL_TX0: R5.2, U1.37 (TXD0)
/RTS: Q1.2 (E), R3.1, U3.19 (~RTS)
/USB_D1+: U2.1 (D1+), U3.8 (USBDP)
/USB_D1-: U2.2 (D1-), U3.9 (USBDM)
/USB_D2+: U1.14 (IO20), U2.3 (D2+)
/USB_D2-: U1.13 (IO19), U2.4 (D2-)
/USB_D+: D1.2 (A2), U2.8 (D+)
/USB_D-: D2.2 (A2), U2.7 (D-)
GND: C1.2, C2.2, C3.2, C4.2, D1.1 (A1), D2.1 (A1), JP1.3 (B), SW1.1, U1.1 (GND), U1.40 (GND), U1.41 (GND), U2.5 (GND), U2.6 (~OE), U3.3 (GND), U3.13 (GND), U3.21 (GND)
unnamed: JP1.2 (C), U2.9 (S)
unnamed: Q1.1 (B), R2.2
unnamed: Q2.1 (B), R3.2
unnamed: R1.1, R4.1, SW1.2
unnamed: R6.1, U3.1 (RXD)
unnamed: R5.1, U3.17 (TXD)
